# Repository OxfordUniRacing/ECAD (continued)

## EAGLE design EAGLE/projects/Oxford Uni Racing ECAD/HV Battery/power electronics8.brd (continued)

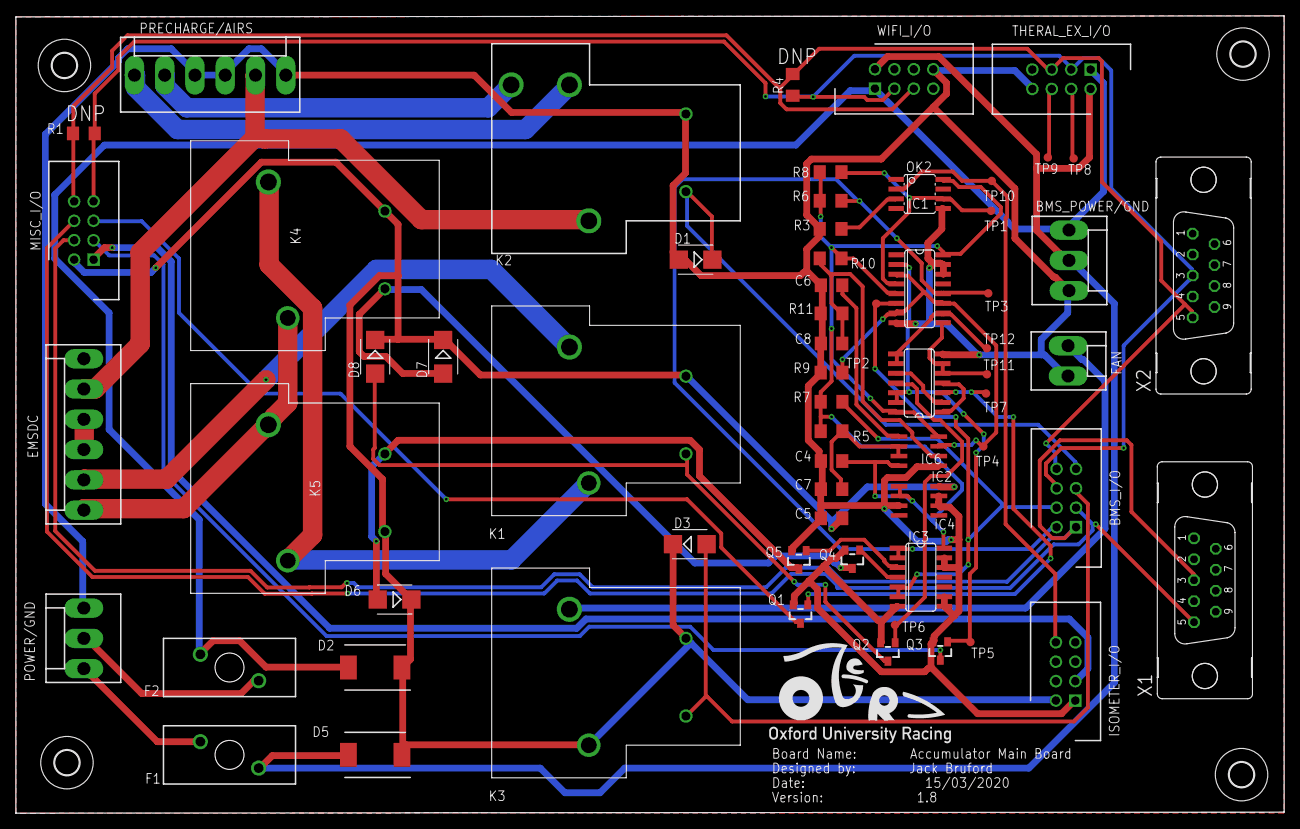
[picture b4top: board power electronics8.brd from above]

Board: 2 copper layers, 165.9 x 104.3 mm, 68 parts (0 on the bottom side), 47 nets.

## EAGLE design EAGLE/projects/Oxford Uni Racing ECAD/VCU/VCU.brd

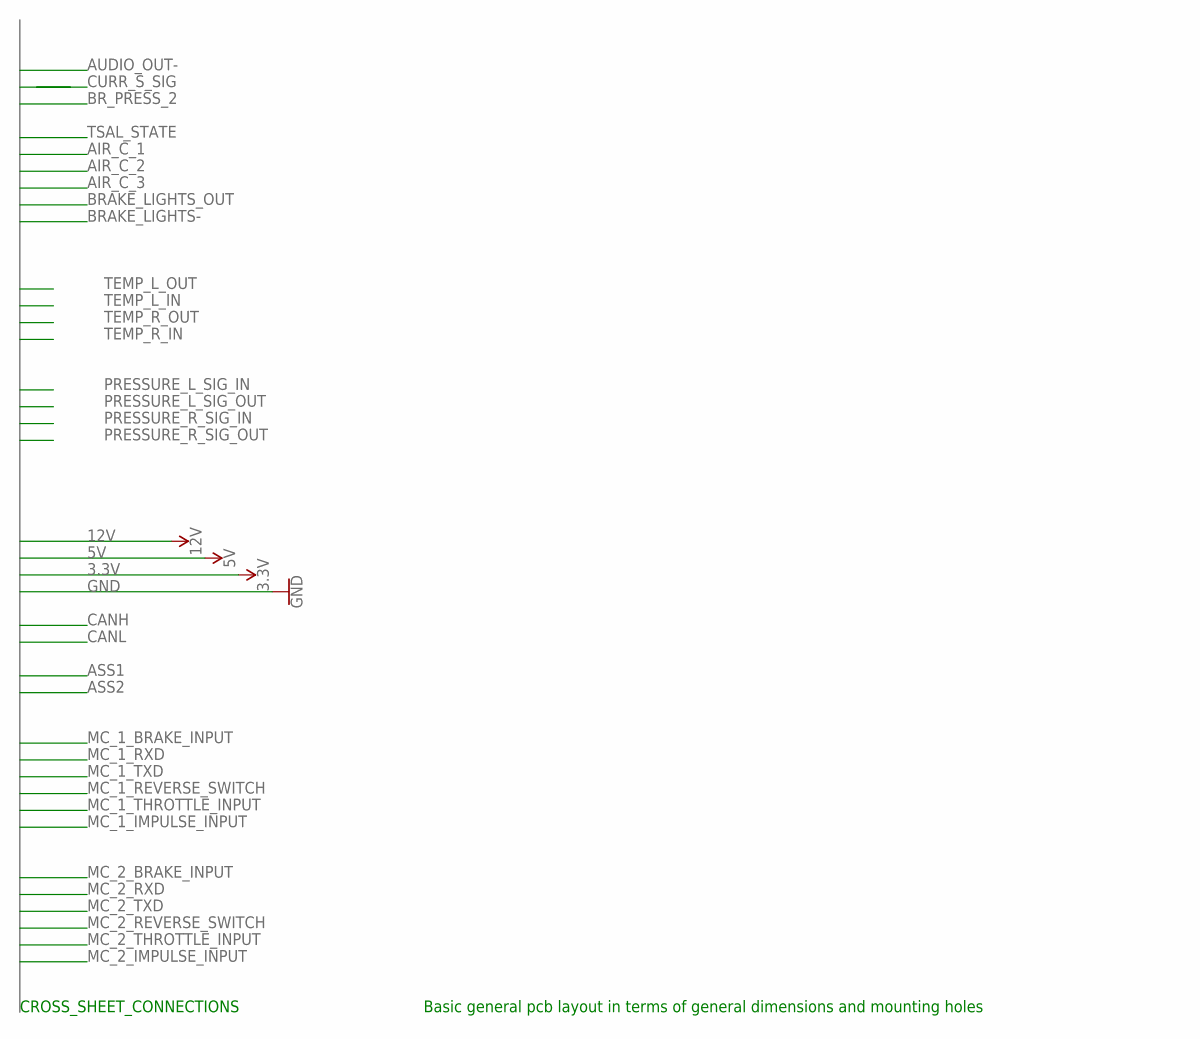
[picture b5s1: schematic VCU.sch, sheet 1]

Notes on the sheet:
Basic general pcb layout in terms of general dimensions and mounting holes
CROSS_SHEET_CONNECTIONS

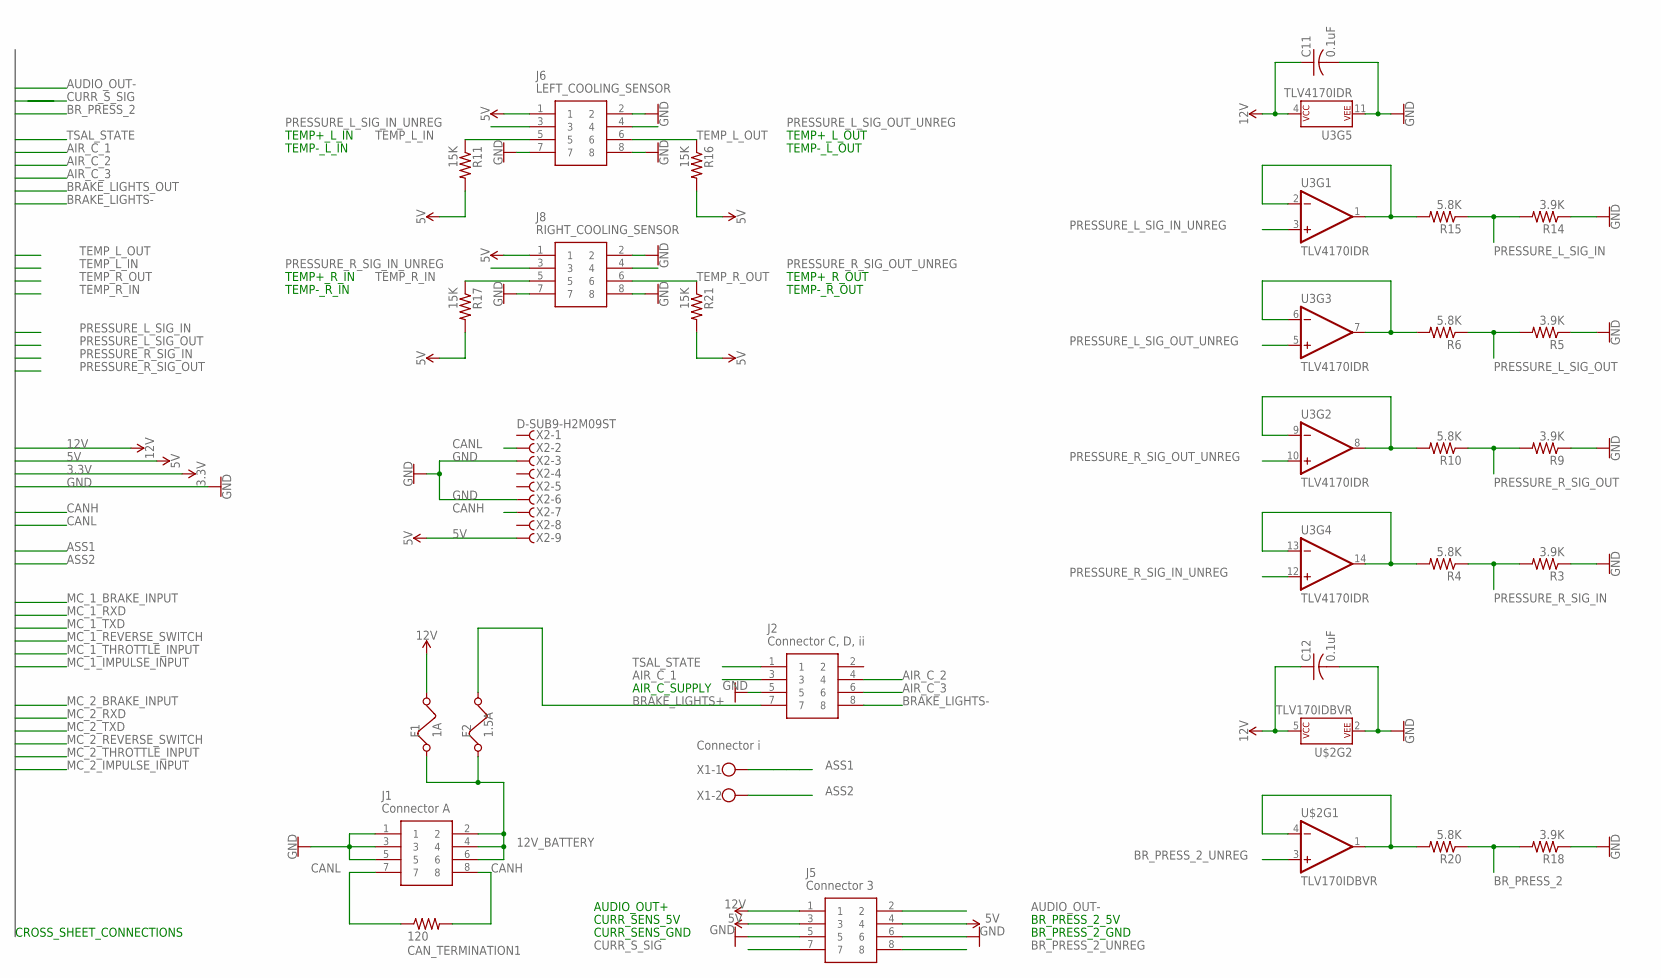
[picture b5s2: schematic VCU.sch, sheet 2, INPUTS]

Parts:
C11, C12: 0.1uF; C050-024X044
CAN_TERMINATION1: 120; R0805
F1: 1A; FUSE
F2: 1.5A; FUSE
J1: Connector A; HDRV8W64P254_2X4_1778X895X915P
J2: Connector C, D, ii; HDRV8W64P254_2X4_1778X895X915P
J5: Connector 3; HDRV8W64P254_2X4_1778X895X915P
J6: LEFT_COOLING_SENSOR; HDRV8W64P254_2X4_1778X895X915P
J8: RIGHT_COOLING_SENSOR; HDRV8W64P254_2X4_1778X895X915P
R3, R5, R9, R14, R18: 3.9K; R0805
R4, R6, R10, R15, R20: 5.8K; R0805
R11, R16, R17, R21: 15K; R0805
U3: TLV4170IDR; SO14
U$2: TLV170IDBVR; SOT23-5
X1: Connector i; W237-102
X2: D-SUB9-H2M09ST; H2M09ST

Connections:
5V: J5.3, J5.4, J6.1, J8.1, R11.2, R16.2, R17.2, R21.2, X2.9; also elsewhere on the board
12V_BATTERY: F1.1, F2.1, J1.2, J1.4, J1.6
AIR_C_1: J2.3; also elsewhere on the board
AIR_C_2: J2.4; also elsewhere on the board
AIR_C_3: J2.6; also elsewhere on the board
ASS1: X1.1; also elsewhere on the board
ASS2: X1.2; also elsewhere on the board
CANH: CAN_TERMINATION1.2, J1.8, X2.7; also elsewhere on the board
CANL: CAN_TERMINATION1.1, J1.7, X2.2; also elsewhere on the board
GND: C11.2, C12.2, J1.1, J1.3, J1.5, J2.5, J5.5, J5.6, J6.2, J6.7, J6.8, J8.2, J8.7, J8.8, R3.1, R5.1, R9.1, R14.1, R18.1, U3.11 (P$V-), U$2.2 (P$V-), X2.3, X2.6; also elsewhere on the board
unnamed: R4.2, U3.13 (-IN), U3.14 (OUT)
unnamed: R6.2, U3.6 (-IN), U3.7 (OUT)
unnamed: R10.2, U3.8 (OUT), U3.9 (-IN)
unnamed: R15.2, U3.1 (OUT), U3.2 (-IN)
unnamed: J5.8, U$2.3 (+IN)
unnamed: R18.2, R20.1
unnamed: R20.2, U$2.1 (OUT), U$2.4 (-IN)
PRESSURE_L_SIG_IN: R14.2, R15.1; also elsewhere on the board
PRESSURE_L_SIG_IN_UNREG: J6.3, U3.3 (+IN)
PRESSURE_L_SIG_OUT: R5.2, R6.1; also elsewhere on the board
PRESSURE_L_SIG_OUT_UNREG: J6.4, U3.5 (+IN)
PRESSURE_R_SIG_IN: R3.2, R4.1; also elsewhere on the board
PRESSURE_R_SIG_IN_UNREG: J8.3, U3.12 (+IN)
PRESSURE_R_SIG_OUT: R9.2, R10.1; also elsewhere on the board
PRESSURE_R_SIG_OUT_UNREG: J8.4, U3.10 (+IN)
TEMP_L_IN: J6.5, R11.1; also elsewhere on the board
TEMP_L_OUT: J6.6, R16.1; also elsewhere on the board
TEMP_R_IN: J8.5, R17.1; also elsewhere on the board
TEMP_R_OUT: J8.6, R21.1; also elsewhere on the board
TSAL_STATE: J2.1; also elsewhere on the board

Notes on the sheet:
CROSS_SHEET_CONNECTIONS
TEMP+_L_IN
TEMP-_L_IN
TEMP+_R_IN
TEMP-_R_IN
AIR_C_SUPPLY
CURR_SENS_5V
CURR_SENS_GND
BR_PRESS_2_5V
BR_PRESS_2_GND
AUDIO_OUT+
TEMP+_R_OUT
TEMP-_R_OUT
TEMP-_L_OUT
TEMP+_L_OUT

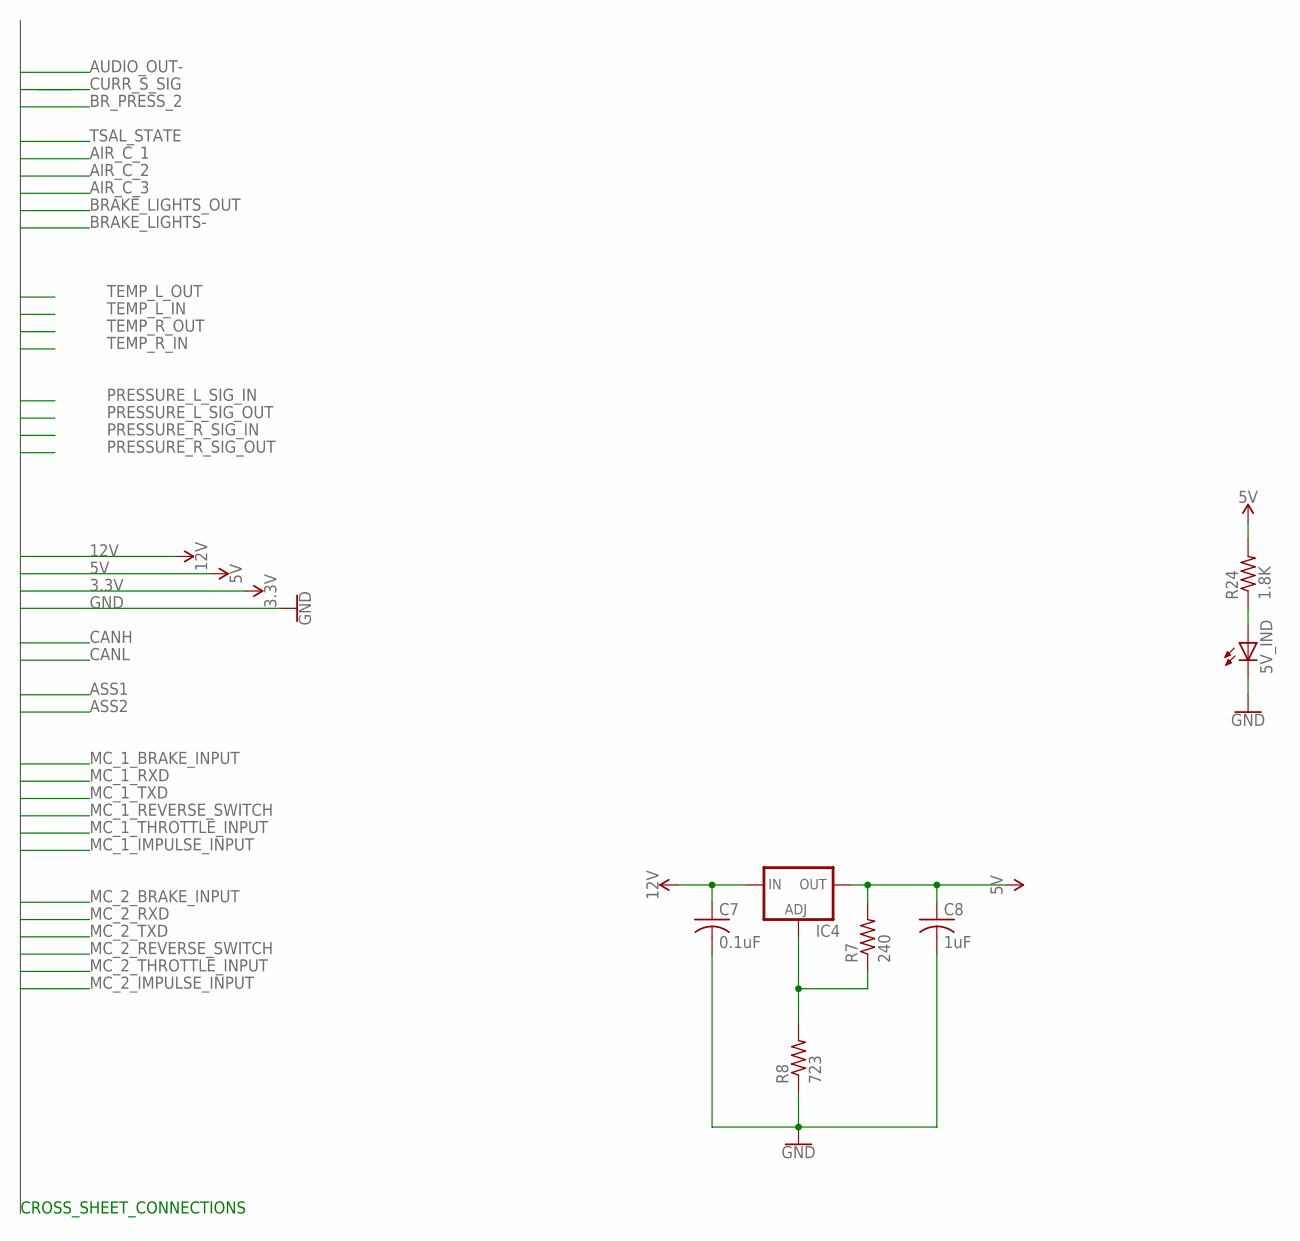
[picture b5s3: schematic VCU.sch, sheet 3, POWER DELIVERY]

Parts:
5V_IND: LED3MM
C7: 0.1uF; C050-025X075
C8: 1uF; C050-025X075
IC4: LM317TS; 317TS
R7: 240; R0805
R8: 723; R0805
R24: 1.8K; R0805

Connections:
5V: C8.1, IC4.2 (OUT), R7.2, R24.2; also elsewhere on the board
GND: 5V_IND.K (C), C7.2, C8.2, R8.1; also elsewhere on the board
unnamed: 5V_IND.A, R24.1
unnamed: IC4.1 (ADJ), R7.1, R8.2

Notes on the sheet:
CROSS_SHEET_CONNECTIONS

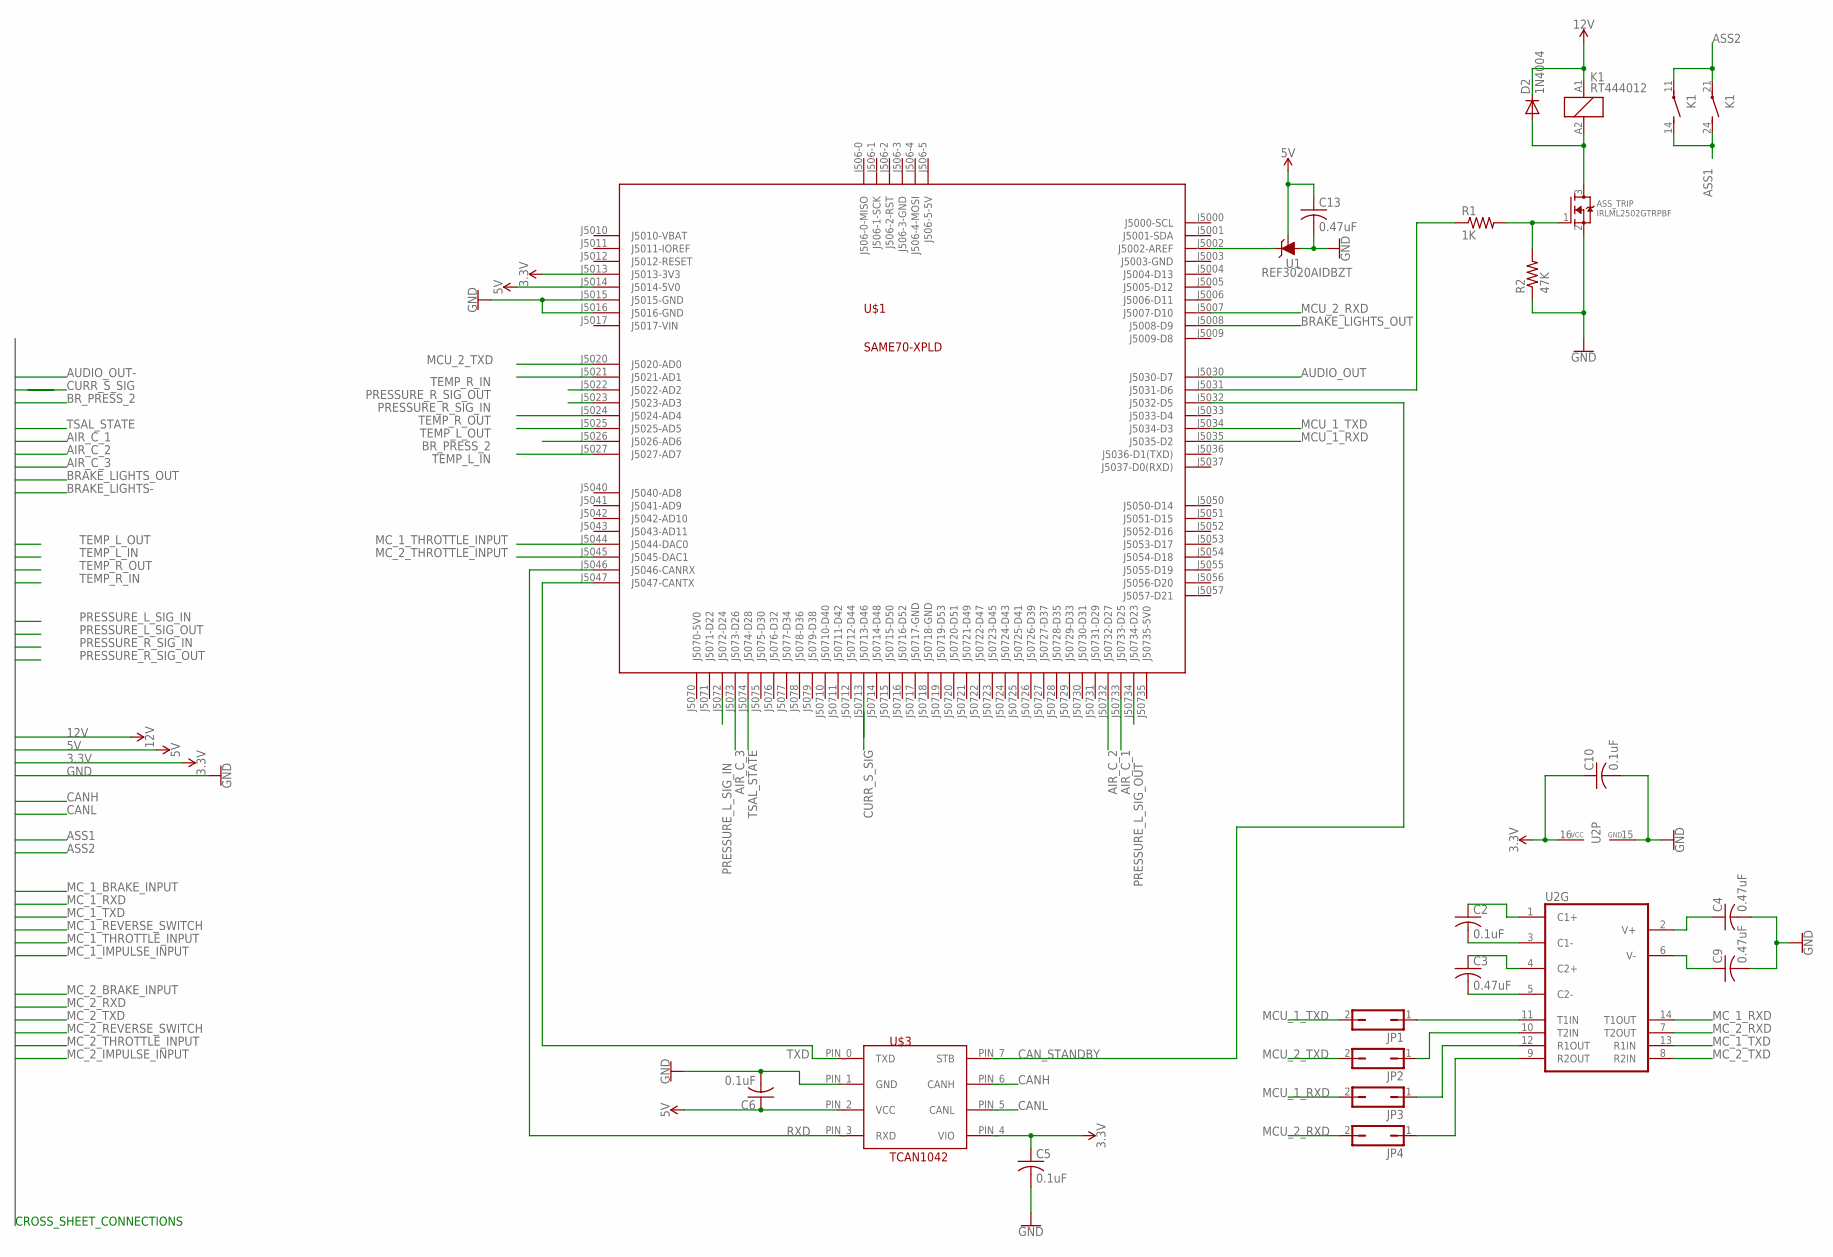
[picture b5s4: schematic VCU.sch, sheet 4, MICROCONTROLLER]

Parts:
ASS_TRIP: IRLML2502GTRPBF; SOT23
C2, C5, C6, C10: 0.1uF; C025-024X044
C3, C4, C9: 0.47uF; C025-024X044
C13: 0.47uF; C050-024X044
D2: 1N4004; DO41-10
JP1, JP2, JP3, JP4: JP1Q; JP1
K1: RT444012; RT2N/O
R1: 1K; R0805
R2: 47K; R0805
U1: REF3020AIDBZT; SOT23-3
U2: MAX3232S; SO16
U$1: SAME70-XPLD
U$3: TCAN1042

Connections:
3.3V: C5.1, C10.1, U2.16 (VCC), U$1.J5013 (J5013-3V3), U$3.PIN_4 (VIO)
5V: C6.1, C13.1, U1.1 (ADJ), U$1.J5014 (J5014-5V0), U$3.PIN_2 (VCC); also elsewhere on the board
AIR_C_1: U$1.J50733 (J50733-D25); also elsewhere on the board
AIR_C_2: U$1.J50732 (J50732-D27); also elsewhere on the board
AIR_C_3: U$1.J5073 (J5073-D26); also elsewhere on the board
ASS1: K1.14 (S), K1.24 (S); also elsewhere on the board
ASS2: K1.11, K1.21; also elsewhere on the board
AUDIO_OUT: U$1.J5030 (J5030-D7); also elsewhere on the board
BRAKE_LIGHTS_OUT: U$1.J5008 (J5008-D9); also elsewhere on the board
BR_PRESS_2: U$1.J5026 (J5026-AD6)
CANH: U$3.PIN_6 (CANH); also elsewhere on the board
CANL: U$3.PIN_5 (CANL); also elsewhere on the board
CAN_STANDBY: U$1.J5032 (J5032-D5), U$3.PIN_7 (STB)
CURR_S_SIG: U$1.J50713 (J50713-D46)
GND: ASS_TRIP.2 (S), C4.2, C5.2, C6.2, C9.2, C10.2, C13.2, R2.1, U1.3 (A), U2.15 (GND), U$1.J5015 (J5015-GND), U$1.J5016 (J5016-GND), U$3.PIN_1 (GND); also elsewhere on the board
MCU_1_RXD: JP3.2, U$1.J5035 (J5035-D2)
MCU_1_TXD: JP1.2, U$1.J5034 (J5034-D3)
MCU_2_RXD: JP4.2, U$1.J5007 (J5007-D10)
MCU_2_TXD: JP2.2, U$1.J5020 (J5020-AD0)
MC_1_RXD: U2.14 (T1OUT); also elsewhere on the board
MC_1_THROTTLE_INPUT: U$1.J5044 (J5044-DAC0)
MC_1_TXD: U2.13 (R1IN); also elsewhere on the board
MC_2_RXD: U2.7 (T2OUT); also elsewhere on the board
MC_2_THROTTLE_INPUT: U$1.J5045 (J5045-DAC1)
MC_2_TXD: U2.8 (R2IN); also elsewhere on the board
unnamed: R1.1, U$1.J5031 (J5031-D6)
unnamed: ASS_TRIP.1 (G), R1.2, R2.2
unnamed: ASS_TRIP.3 (D), D2.A, K1.A2 (2)
unnamed: C3.2, U2.5 (C2-)
unnamed: C3.1, U2.4 (C2+)
unnamed: C2.2, U2.3 (C1-)
unnamed: C2.1, U2.1 (C1+)
unnamed: U1.2 (C), U$1.J5002 (J5002-AREF)
unnamed: C4.1, U2.2 (V+)
unnamed: C9.1, U2.6 (V-)
unnamed: JP1.1, U2.11 (T1IN)
unnamed: JP2.1, U2.10 (T2IN)
unnamed: JP3.1, U2.12 (R1OUT)
unnamed: JP4.1, U2.9 (R2OUT)
PRESSURE_L_SIG_IN: U$1.J5072 (J5072-D24); also elsewhere on the board
PRESSURE_L_SIG_OUT: U$1.J50734 (J50734-D23); also elsewhere on the board
PRESSURE_R_SIG_IN: U$1.J5023 (J5023-AD3); also elsewhere on the board
PRESSURE_R_SIG_OUT: U$1.J5022 (J5022-AD2); also elsewhere on the board
RXD: U$1.J5046 (J5046-CANRX), U$3.PIN_3 (RXD)
TEMP_L_IN: U$1.J5027 (J5027-AD7); also elsewhere on the board
TEMP_L_OUT: U$1.J5025 (J5025-AD5); also elsewhere on the board
TEMP_R_IN: U$1.J5021 (J5021-AD1); also elsewhere on the board
TEMP_R_OUT: U$1.J5024 (J5024-AD4); also elsewhere on the board
TSAL_STATE: U$1.J5074 (J5074-D28); also elsewhere on the board
TXD: U$1.J5047 (J5047-CANTX), U$3.PIN_0 (TXD)

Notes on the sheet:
CROSS_SHEET_CONNECTIONS

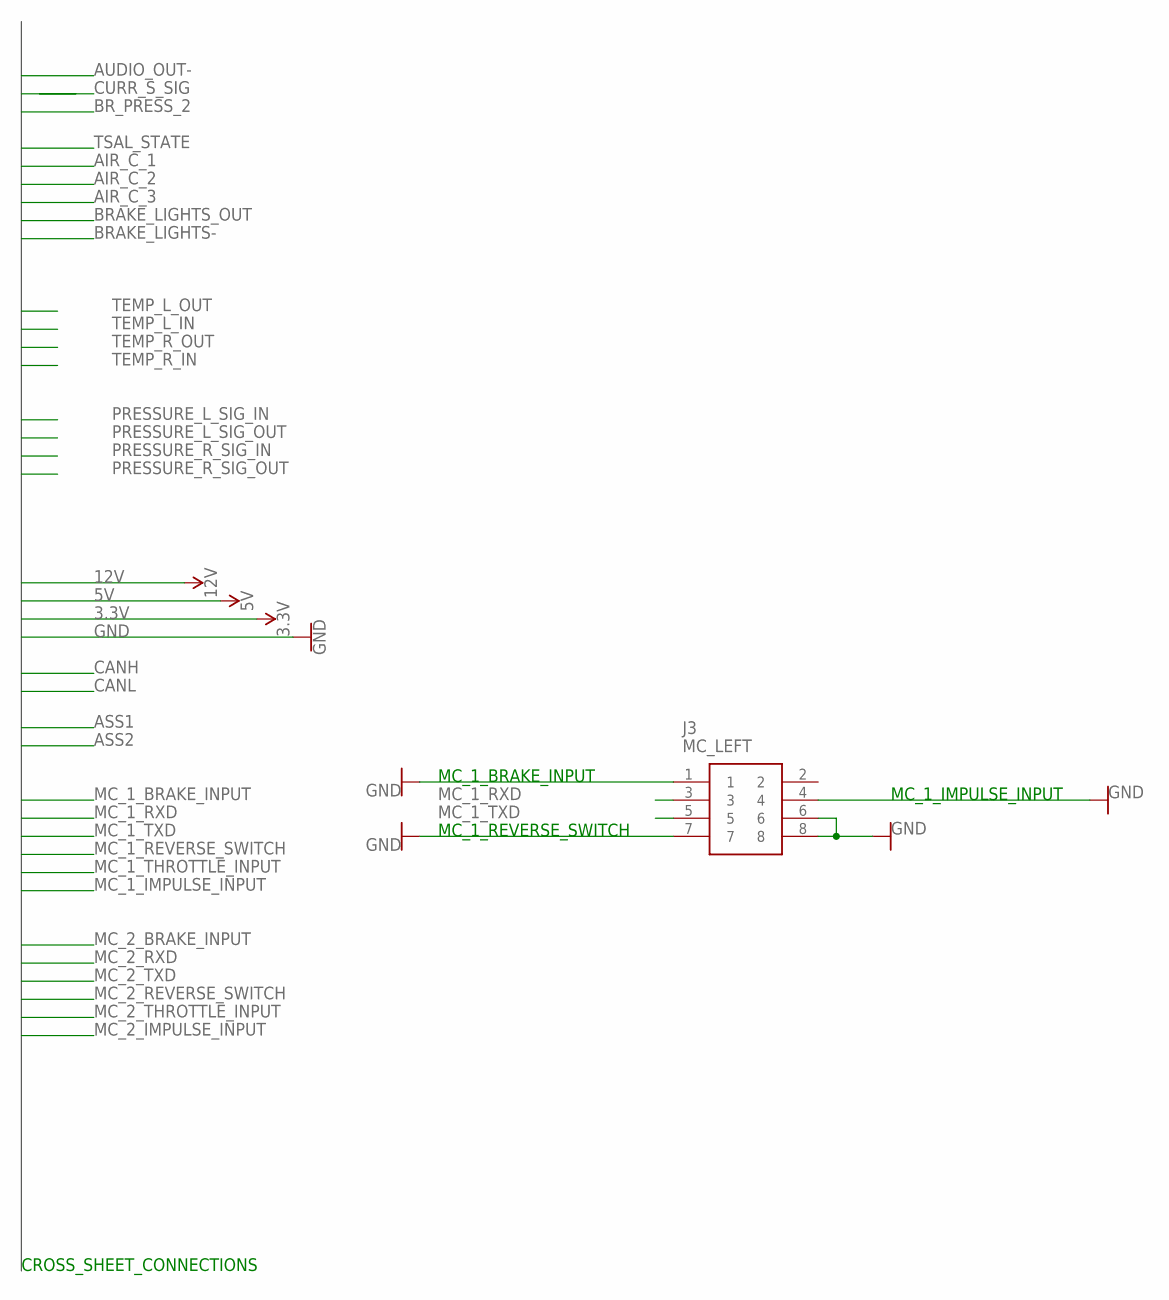
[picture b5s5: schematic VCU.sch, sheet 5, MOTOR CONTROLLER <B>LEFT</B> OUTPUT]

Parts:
J3: MC_LEFT; HDRV8W64P254_2X4_1778X895X915P

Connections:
GND: J3.1, J3.4, J3.6, J3.7, J3.8; also elsewhere on the board
MC_1_RXD: J3.3; also elsewhere on the board
MC_1_TXD: J3.5; also elsewhere on the board

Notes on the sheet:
MC_1_BRAKE_INPUT
MC_1_REVERSE_SWITCH
MC_1_IMPULSE_INPUT
CROSS_SHEET_CONNECTIONS

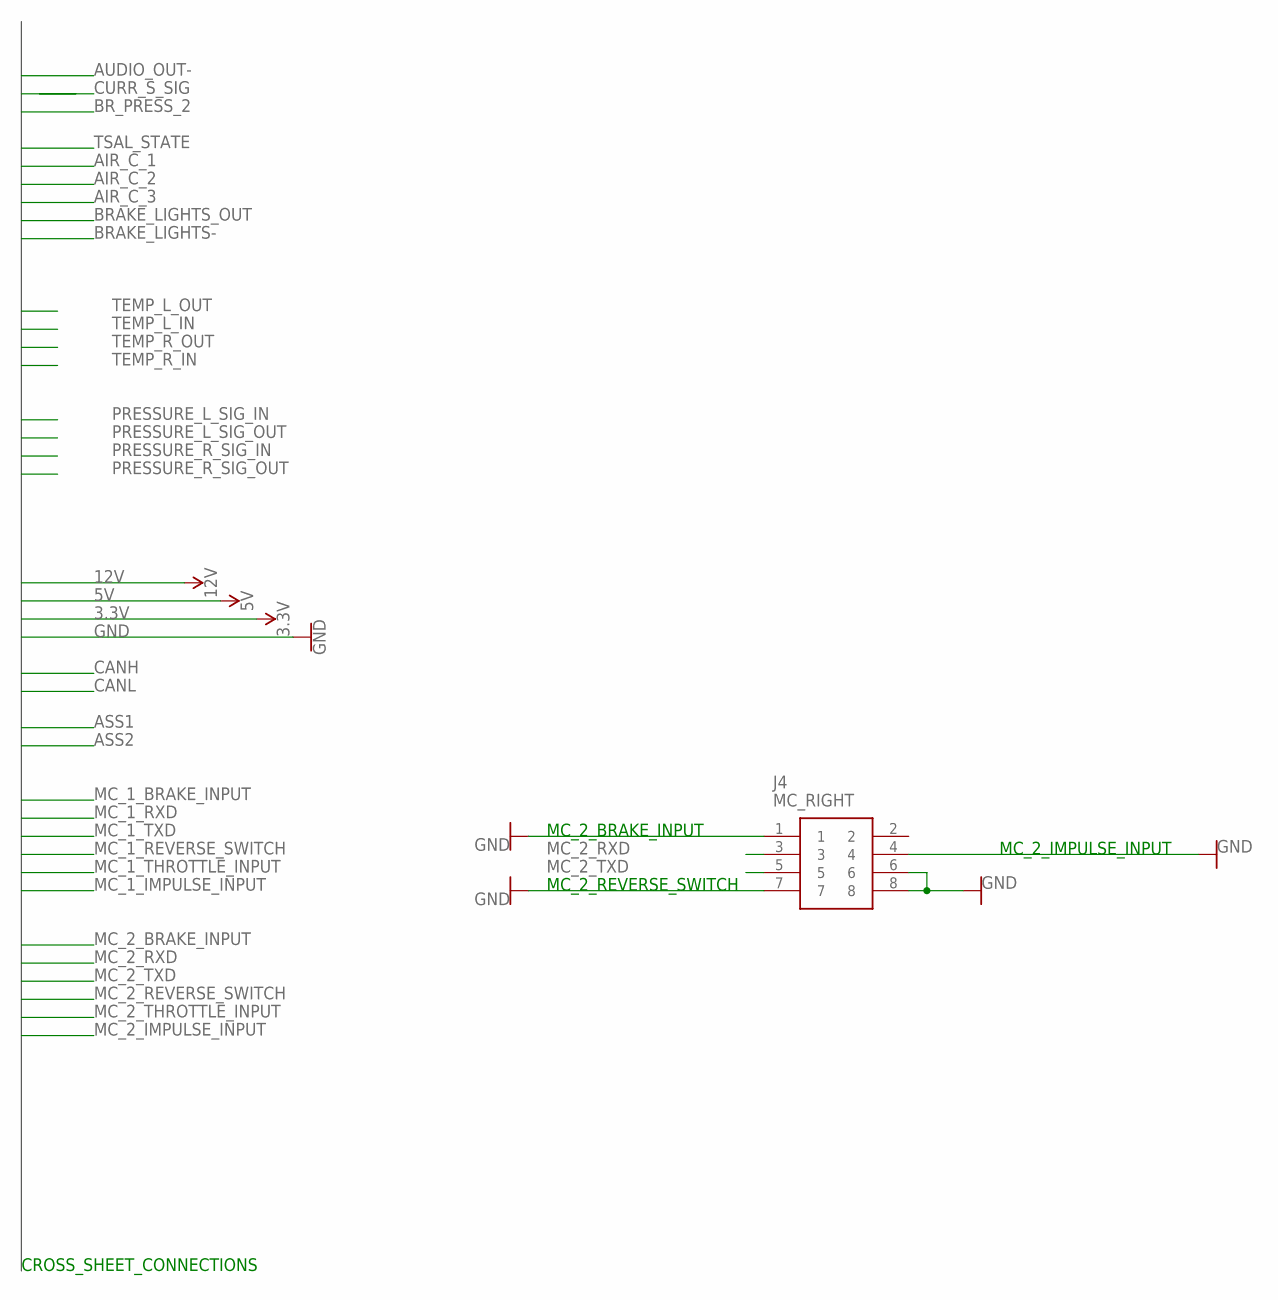
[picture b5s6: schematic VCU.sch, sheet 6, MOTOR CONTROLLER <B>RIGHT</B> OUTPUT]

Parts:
J4: MC_RIGHT; HDRV8W64P254_2X4_1778X895X915P

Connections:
GND: J4.1, J4.4, J4.6, J4.7, J4.8; also elsewhere on the board
MC_2_RXD: J4.3; also elsewhere on the board
MC_2_TXD: J4.5; also elsewhere on the board

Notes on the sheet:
MC_2_BRAKE_INPUT
MC_2_REVERSE_SWITCH
MC_2_IMPULSE_INPUT
CROSS_SHEET_CONNECTIONS

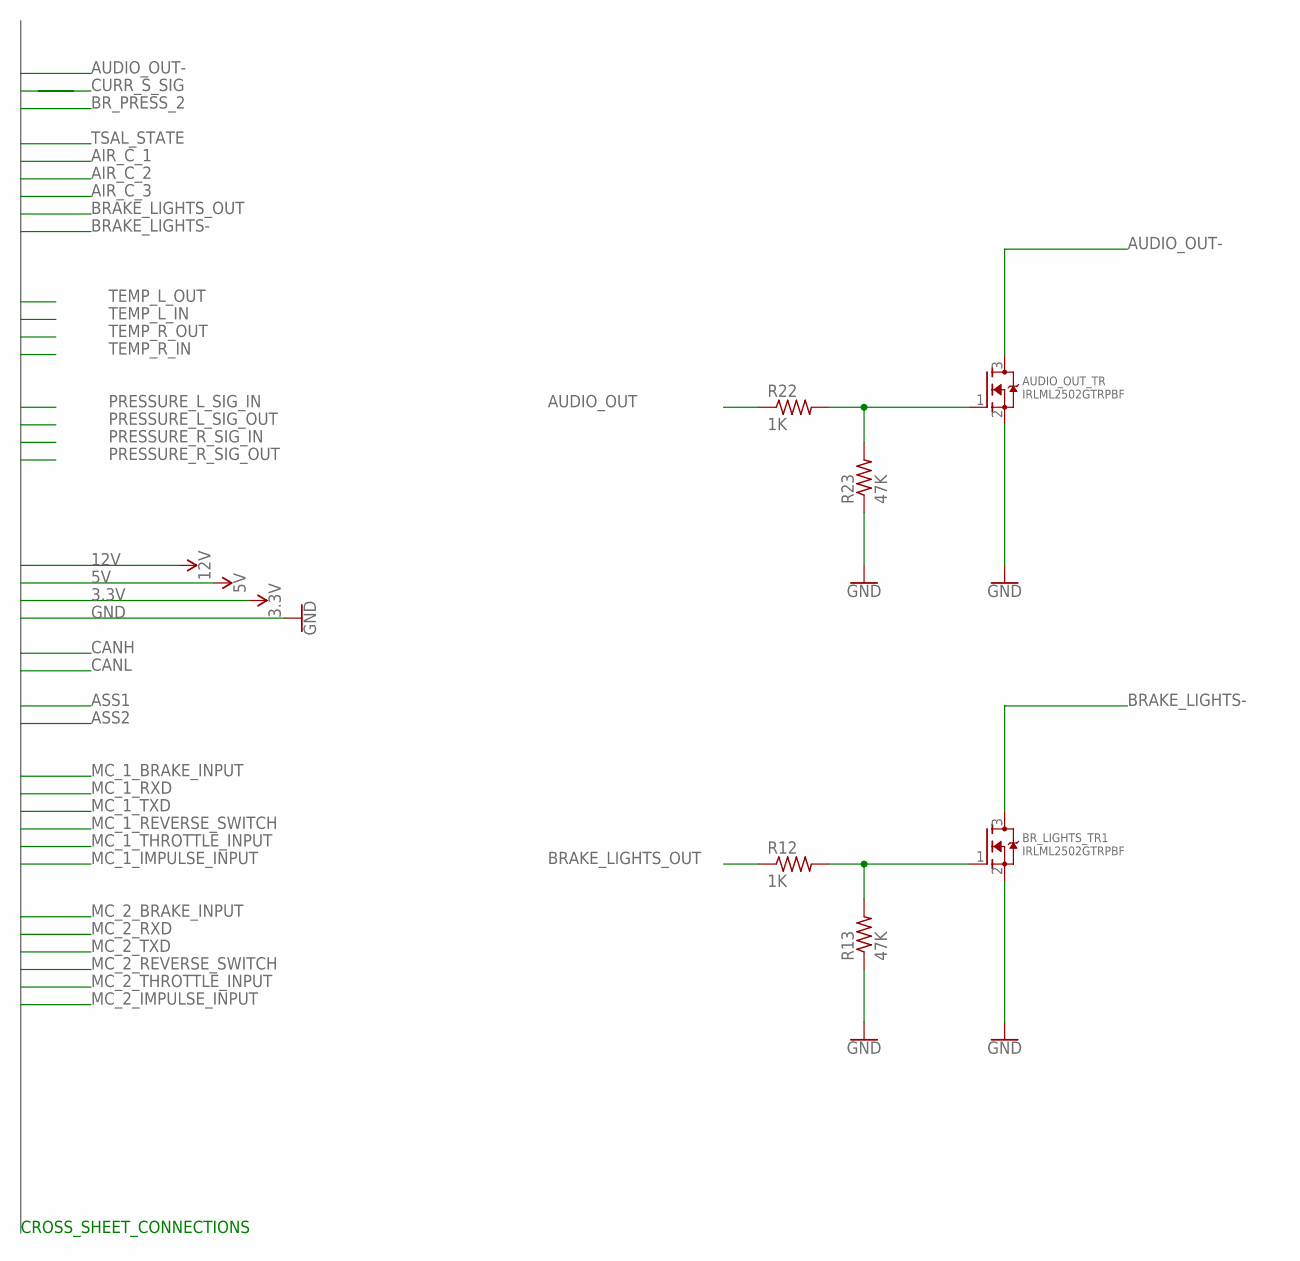
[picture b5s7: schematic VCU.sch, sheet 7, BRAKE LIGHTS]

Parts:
AUDIO_OUT_TR: IRLML2502GTRPBF; SOT23
BR_LIGHTS_TR1: IRLML2502GTRPBF; SOT23
R12, R22: 1K; R0805
R13, R23: 47K; R0805

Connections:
AUDIO_OUT: R22.1; also elsewhere on the board
BRAKE_LIGHTS-: BR_LIGHTS_TR1.3 (D); also elsewhere on the board
BRAKE_LIGHTS_OUT: R12.1; also elsewhere on the board
GND: AUDIO_OUT_TR.2 (S), BR_LIGHTS_TR1.2 (S), R13.1, R23.1; also elsewhere on the board
unnamed: AUDIO_OUT_TR.1 (G), R22.2, R23.2
unnamed: BR_LIGHTS_TR1.1 (G), R12.2, R13.2

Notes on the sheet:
CROSS_SHEET_CONNECTIONS

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
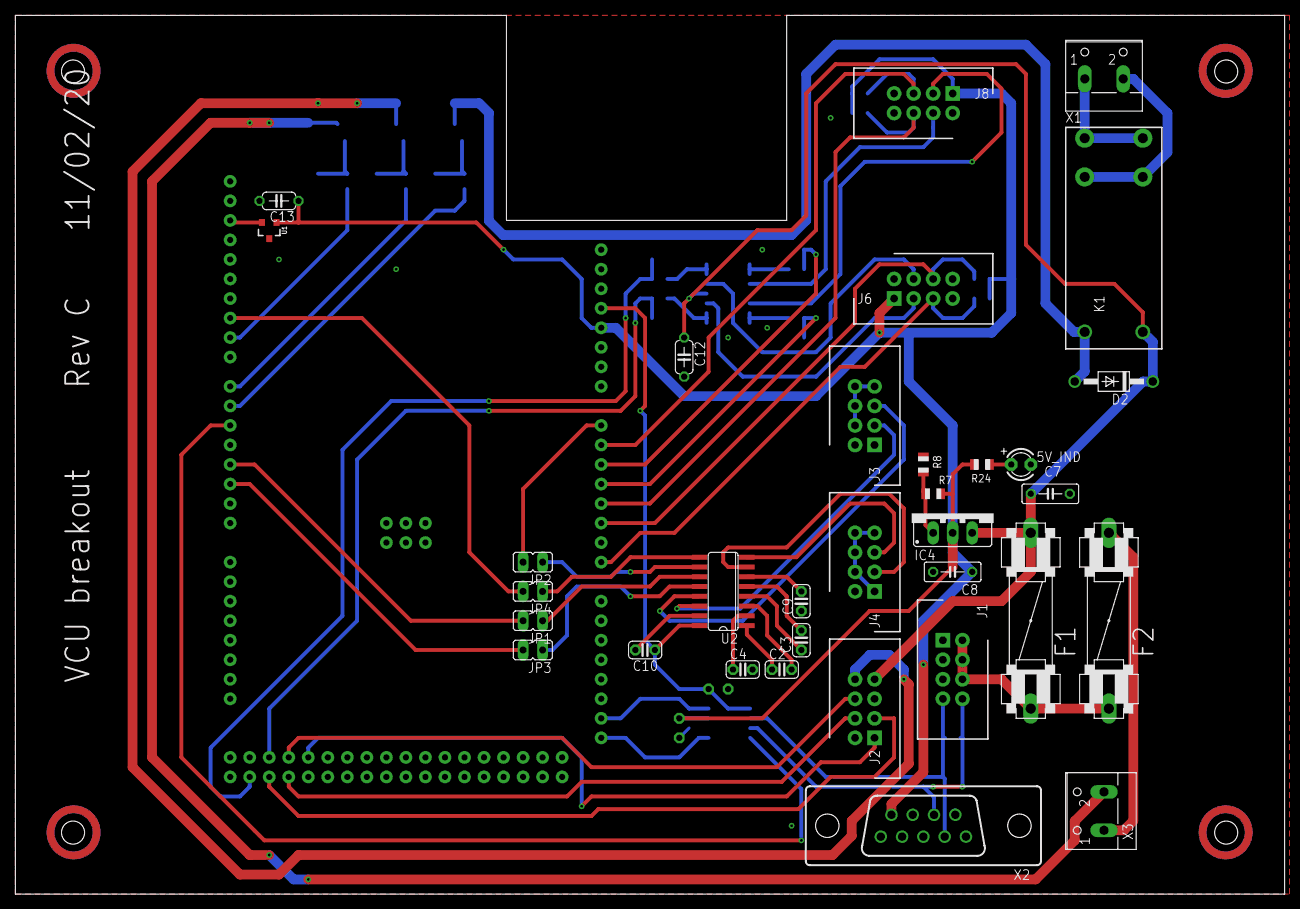
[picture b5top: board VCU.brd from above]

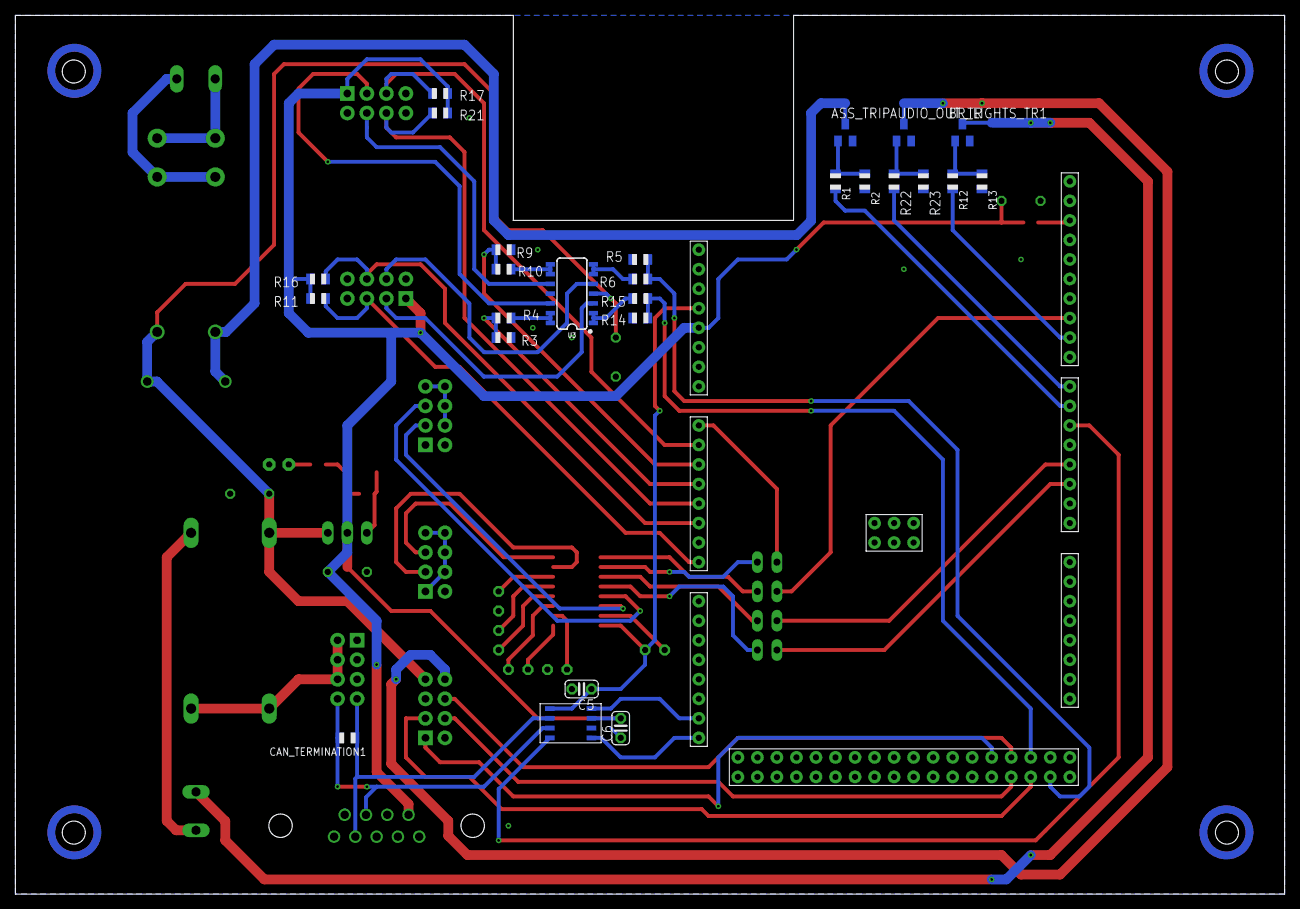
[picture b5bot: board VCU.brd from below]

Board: 2 copper layers, 165.1 x 114.3 mm, 60 parts (27 on the bottom side), 63 nets.

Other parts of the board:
X3: Brake Lights; W237-102

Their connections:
BRAKE_LIGHTS-: X3.2; also elsewhere on the board
